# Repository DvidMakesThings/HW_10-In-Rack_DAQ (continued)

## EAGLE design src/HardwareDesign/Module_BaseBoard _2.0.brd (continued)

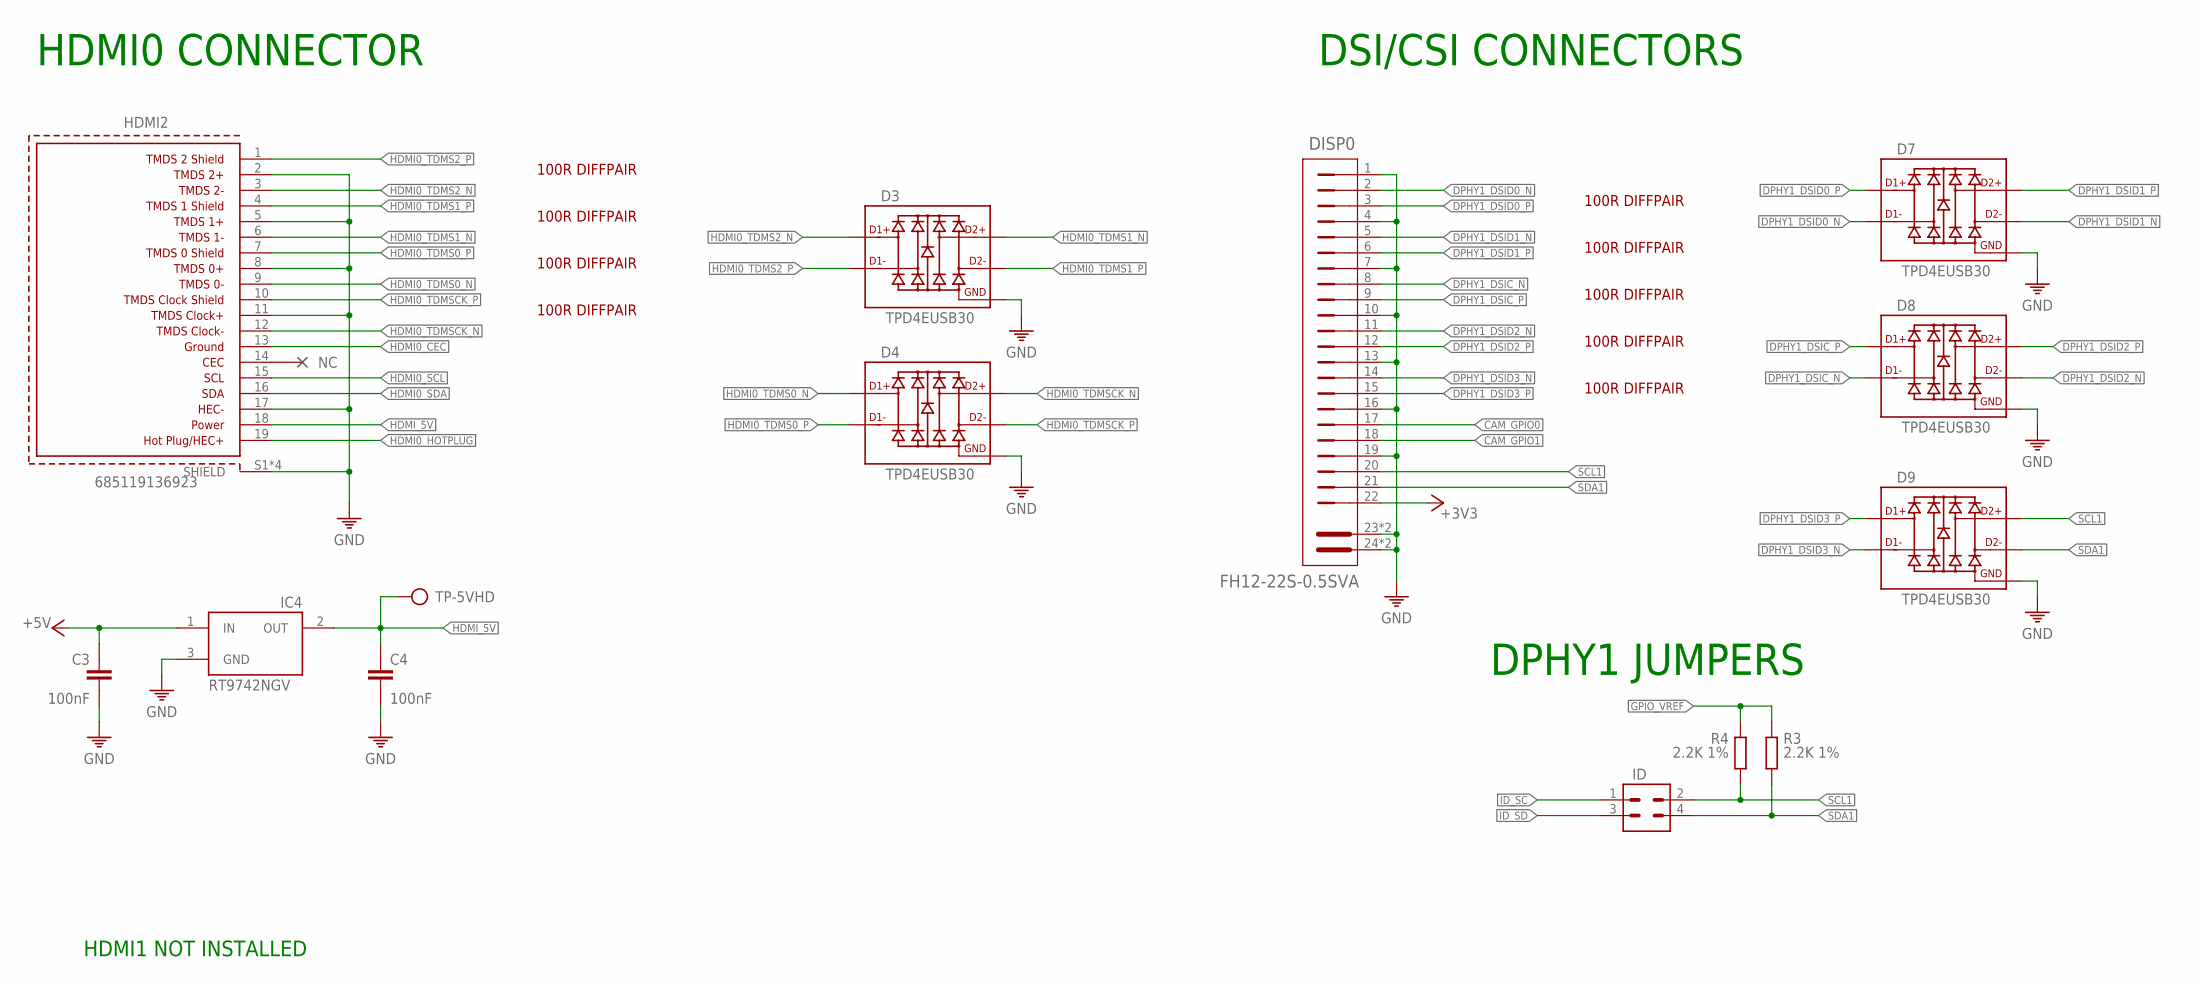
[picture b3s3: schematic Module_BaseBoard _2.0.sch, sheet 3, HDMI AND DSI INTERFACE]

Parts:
C3, C4: 100nF; C0402
D3, D4, D7, D8, D9: TPD4EUSB30; USON
DISP0: FH12-22S-0.5SVA; FH12-22S-0.5SH
HDMI2: 685119136923
IC4: RT9742NGV; SOT23
ID: CON-2X2; 2X2
R3, R4: 2.2K 1%; 0402
TP-5VHD: TP

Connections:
+3V3: DISP0.22; also elsewhere on the board
+5V: C3.1, IC4.1 (IN); also elsewhere on the board
CAM_GPIO0: DISP0.17; also elsewhere on the board
CAM_GPIO1: DISP0.18; also elsewhere on the board
DPHY1_DSIC_N: D8.5 (D2-), D8.6 (D2-), DISP0.8; also elsewhere on the board
DPHY1_DSIC_P: D8.4 (D2+), D8.7 (D2+), DISP0.9; also elsewhere on the board
DPHY1_DSID0_N: D7.5 (D2-), D7.6 (D2-), DISP0.2; also elsewhere on the board
DPHY1_DSID0_P: D7.4 (D2+), D7.7 (D2+), DISP0.3; also elsewhere on the board
DPHY1_DSID1_N: D7.2 (D1-), D7.9 (D1-), DISP0.5; also elsewhere on the board
DPHY1_DSID1_P: D7.1 (D1+), D7.10 (D1+), DISP0.6; also elsewhere on the board
DPHY1_DSID2_N: D8.2 (D1-), D8.9 (D1-), DISP0.11; also elsewhere on the board
DPHY1_DSID2_P: D8.1 (D1+), D8.10 (D1+), DISP0.12; also elsewhere on the board
DPHY1_DSID3_N: D9.5 (D2-), D9.6 (D2-), DISP0.14; also elsewhere on the board
DPHY1_DSID3_P: D9.4 (D2+), D9.7 (D2+), DISP0.15; also elsewhere on the board
GND: C3.2, C4.2, D3.3 (GND), D3.8 (GND), D4.3 (GND), D4.8 (GND), D7.3 (GND), D7.8 (GND), D8.3 (GND), D8.8 (GND), D9.3 (GND), D9.8 (GND), DISP0.1, DISP0.4, DISP0.7, DISP0.10, DISP0.13, DISP0.16, DISP0.19, DISP0.23 (MH1), DISP0.24 (MH2), DISP0.25 (MH1), DISP0.26 (MH2), HDMI2.2 (TMDS2+), HDMI2.5 (TMDSDATA1+), HDMI2.8 (TMDS0+), HDMI2.11 (TMDSCLOCK+), HDMI2.17 (UTILITY/HEAC+), HDMI2.S1 (SHIELD), HDMI2.S2 (SHIELD), HDMI2.S3 (SHIELD), HDMI2.S4 (SHIELD), IC4.3 (GND); also elsewhere on the board
GPIO_VREF: R3.1, R4.1; also elsewhere on the board
HDMI0_CEC: HDMI2.13 (GROUND); also elsewhere on the board
HDMI0_HOTPLUG: HDMI2.19 (HOTPLUG/HEC+); also elsewhere on the board
HDMI0_SCL: HDMI2.15 (SCL); also elsewhere on the board
HDMI0_SDA: HDMI2.16 (SDA); also elsewhere on the board
HDMI0_TDMS0_N: D4.4 (D2+), D4.7 (D2+), HDMI2.9 (TMDS0-); also elsewhere on the board
HDMI0_TDMS0_P: D4.5 (D2-), D4.6 (D2-), HDMI2.7 (TMDS0SHIELD); also elsewhere on the board
HDMI0_TDMS1_N: D3.1 (D1+), D3.10 (D1+), HDMI2.6 (TMDS1-); also elsewhere on the board
HDMI0_TDMS1_P: D3.2 (D1-), D3.9 (D1-), HDMI2.4 (TMDS1SHIELD); also elsewhere on the board
HDMI0_TDMS2_N: D3.4 (D2+), D3.7 (D2+), HDMI2.3 (TMDS2-); also elsewhere on the board
HDMI0_TDMS2_P: D3.5 (D2-), D3.6 (D2-), HDMI2.1 (TMDS2SHIELD); also elsewhere on the board
HDMI0_TDMSCK_N: D4.1 (D1+), D4.10 (D1+), HDMI2.12 (TMDSCLOCK-); also elsewhere on the board
HDMI0_TDMSCK_P: D4.2 (D1-), D4.9 (D1-), HDMI2.10 (TMDSCLOCKSHIELD); also elsewhere on the board
HDMI_5V: C4.1, HDMI2.18 (POWER), IC4.2 (OUT), TP-5VHD.TP
ID_SC: ID.1; also elsewhere on the board
ID_SD: ID.3; also elsewhere on the board
SCL1: D9.1 (D1+), D9.10 (D1+), DISP0.20, ID.2, R4.2
SDA1: D9.2 (D1-), D9.9 (D1-), DISP0.21, ID.4, R3.2

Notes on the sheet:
HDMI0 CONNECTOR
100R DIFFPAIR
DSI/CSI CONNECTORS
DPHY1 JUMPERS
HDMI1 NOT INSTALLED

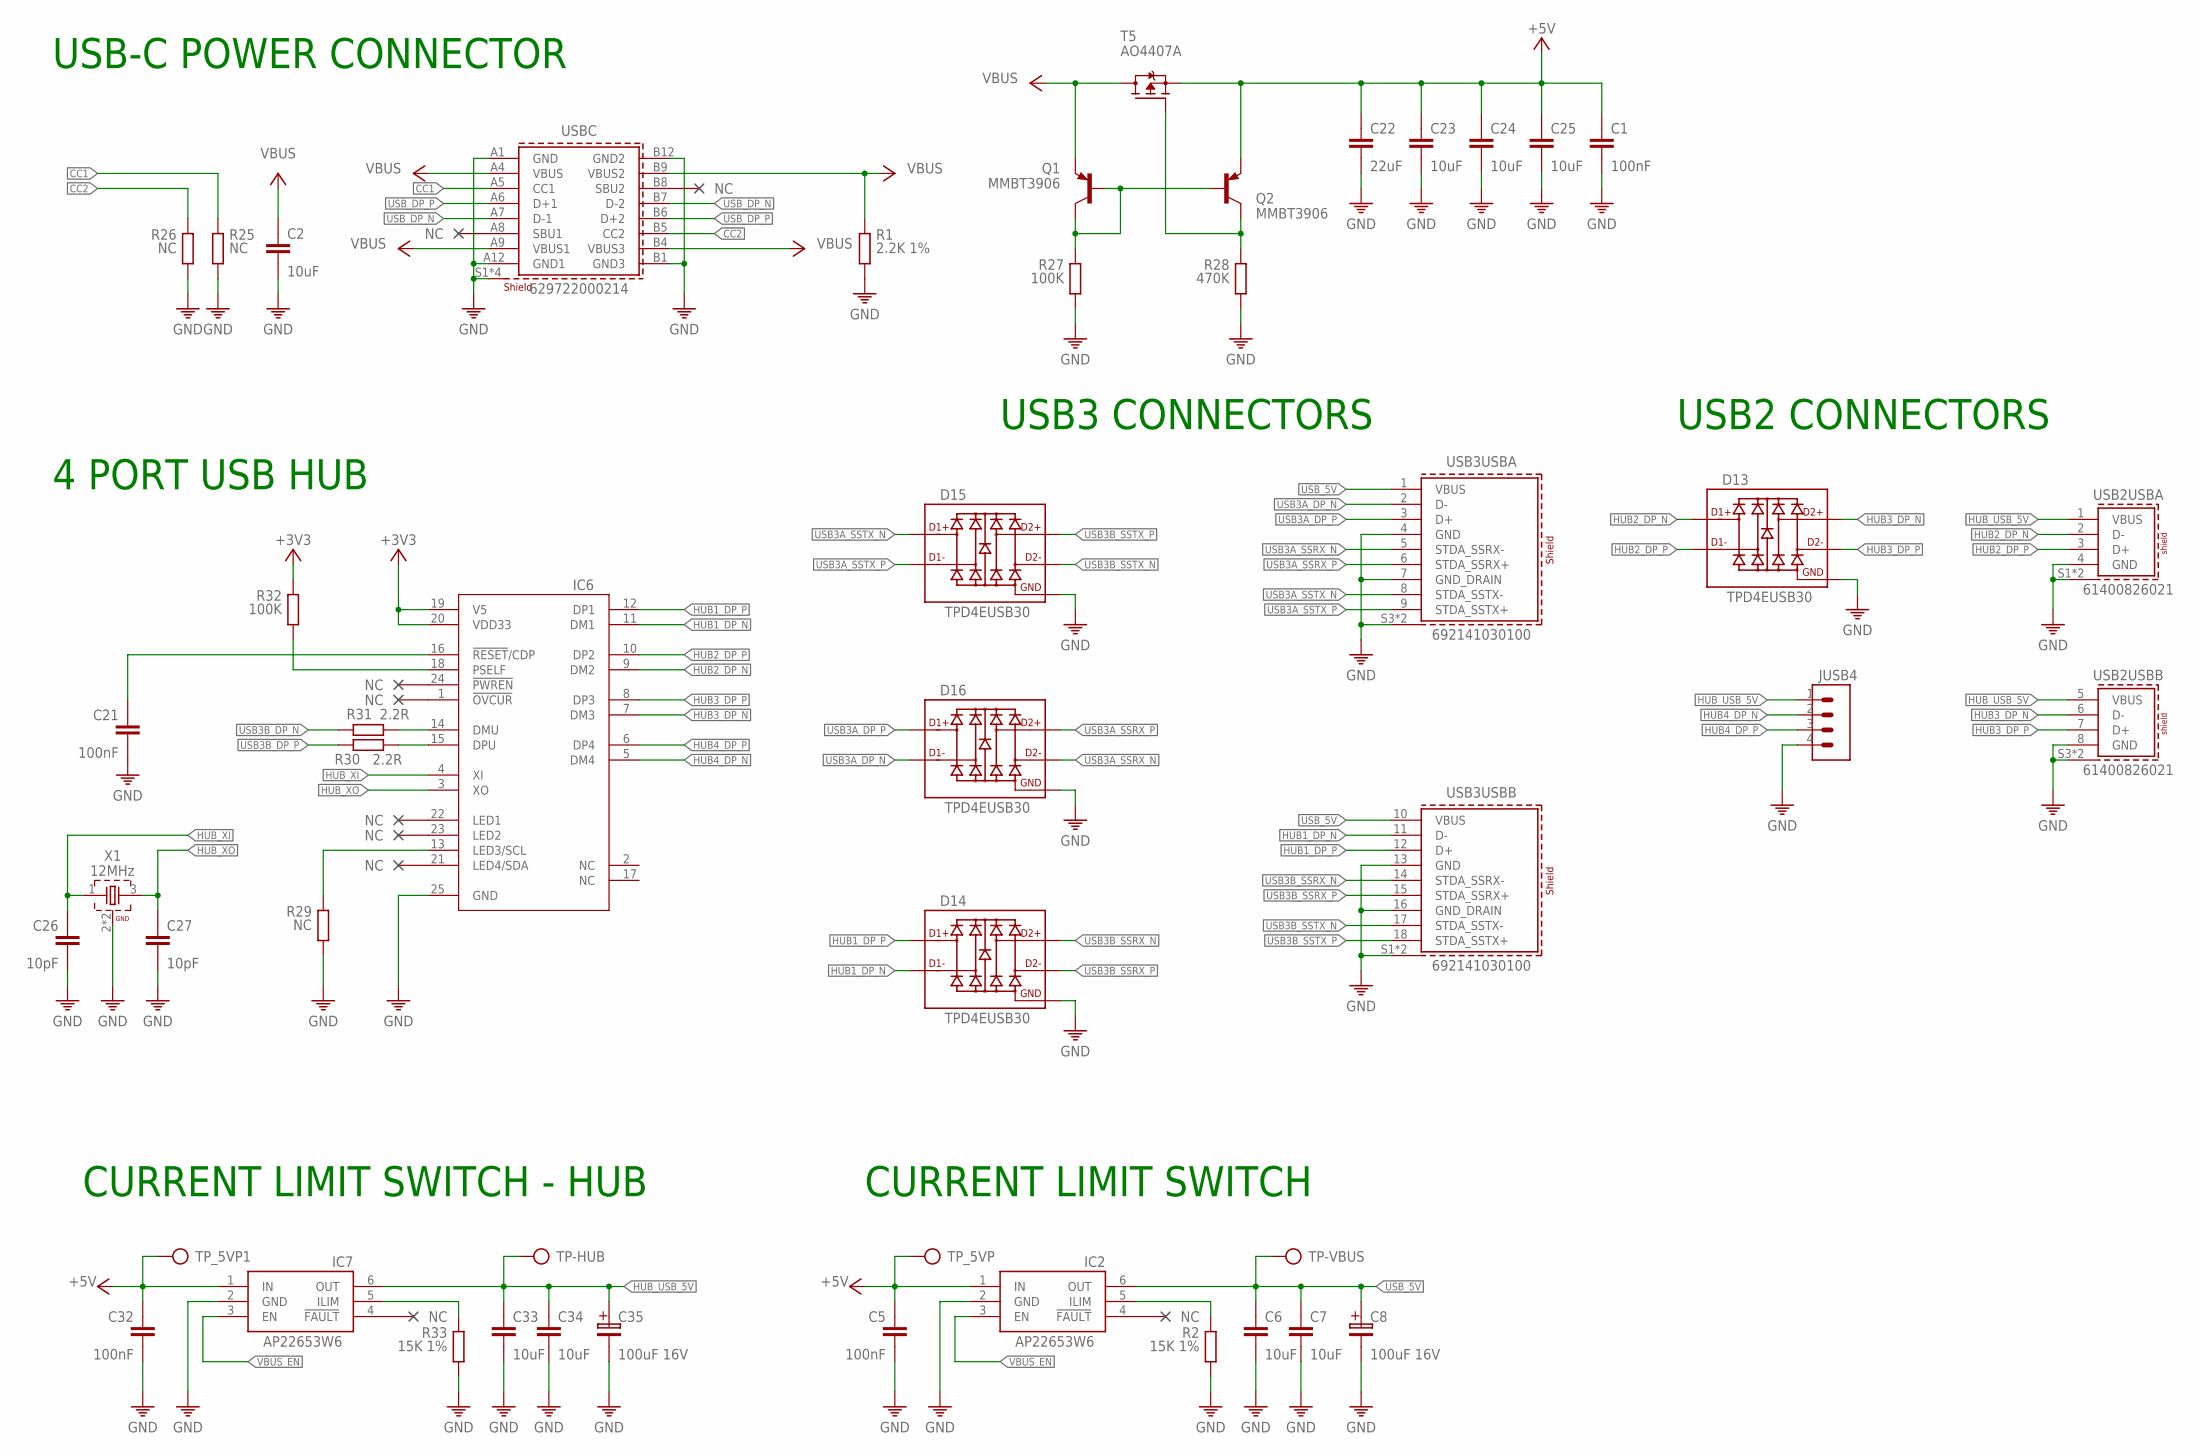
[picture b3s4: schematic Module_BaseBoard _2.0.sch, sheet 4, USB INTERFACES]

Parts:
C1: 100nF; C0805
C2, C6, C7, C23, C24, C25, C33, C34: 10uF; C0805
C5, C21, C32: 100nF; C0402
C8, C35: 100uF 16V; 100UF-16V
C22: 22uF; C0805
C26, C27: 10pF; C0402
D13, D14, D15, D16: TPD4EUSB30; USON
IC2, IC7: AP22653W6; SOT23-6
IC6: CH334; QFN24
JUSB4: CON-1X4; 1X4
Q1, Q2: MMBT3906; SOT23
R1: 2.2K 1%; 0402
R2, R33: 15K 1%; 0402
R25, R26, R29: NC; 0402
R27, R32: 100K; 0402
R28: 470K; 0402
R30, R31: 2.2R; 0402
T5: AO4407A; SO8
TP-HUB: TP
TP-VBUS: TP
TP_5VP, TP_5VP1: TP
USB2: 61400826021
USB3: 692141030100
USBC: 629722000214
X1: 12MHz; WE-XTAL_CFPX-180

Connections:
+3V3: IC6.19 (V5), IC6.20 (VDD33), R32.1; also elsewhere on the board
+5V: C1.1, C5.1, C22.1, C23.1, C24.1, C25.1, C32.1, IC2.1 (IN), IC7.1 (IN), Q2.2 (E), T5.1 (S), T5.2 (S), T5.3 (S), TP_5VP.TP, TP_5VP1.TP; also elsewhere on the board
CC1: R25.1, USBC.A5 (CC1); also elsewhere on the board
CC2: R26.1, USBC.B5 (CC2); also elsewhere on the board
GND: C1.2, C2.2, C5.2, C6.2, C7.2, C8.2, C21.2, C22.2, C23.2, C24.2, C25.2, C26.2, C27.2, C32.2, C33.2, C34.2, C35.2, D13.3 (GND), D13.8 (GND), D14.3 (GND), D14.8 (GND), D15.3 (GND), D15.8 (GND), D16.3 (GND), D16.8 (GND), IC2.2 (GND), IC6.25 (GND), IC7.2 (GND), JUSB4.4, R1.2, R2.2, R25.2, R26.2, R27.2, R28.2, R29.2, R33.2, USB2.4 (GND), USB2.8 (GND), USB2.S1 (SHIELD), USB2.S2 (SHIELD), USB2.S3 (SHIELD), USB2.S4 (SHIELD), USB3.4 (GND), USB3.7 (GND_DRAIN), USB3.13 (GND), USB3.16 (GND_DRAIN), USB3.S1 (SHIELD), USB3.S2 (SHIELD), USB3.S3 (SHIELD), USB3.S4 (SHIELD), USBC.A1 (GND), USBC.A12 (GND1), USBC.B1 (GND3), USBC.B12 (GND2), USBC.S1 (SHIELD), USBC.S2 (SHIELD), USBC.S3 (SHIELD), USBC.S4 (SHIELD), X1.2 (GND), X1.4 (GND); also elsewhere on the board
HUB1_DP_N: D14.5 (D2-), D14.6 (D2-), IC6.11 (DM1), USB3.11 (D-)
HUB1_DP_P: D14.4 (D2+), D14.7 (D2+), IC6.12 (DP1), USB3.12 (D+)
HUB2_DP_N: D13.4 (D2+), D13.7 (D2+), IC6.9 (DM2), USB2.2 (D-)
HUB2_DP_P: D13.5 (D2-), D13.6 (D2-), IC6.10 (DP2), USB2.3 (D+)
HUB3_DP_N: D13.1 (D1+), D13.10 (D1+), IC6.7 (DM3), USB2.6 (D-)
HUB3_DP_P: D13.2 (D1-), D13.9 (D1-), IC6.8 (DP3), USB2.7 (D+)
HUB4_DP_N: IC6.5 (DM4), JUSB4.2
HUB4_DP_P: IC6.6 (DP4), JUSB4.3
HUB_USB_5V: C33.1, C34.1, C35.1, IC7.6 (OUT), JUSB4.1, TP-HUB.TP, USB2.1 (VBUS), USB2.5 (VBUS)
HUB_XI: C26.1, IC6.4 (XI), X1.1
HUB_XO: C27.1, IC6.3 (XO), X1.3 (2)
unnamed: IC2.5 (ILIM), R2.1
unnamed: C21.1, IC6.16 (!RESET!/CDP)
unnamed: Q1.1 (B), Q1.3 (C), Q2.1 (B), R27.1
unnamed: Q2.3 (C), R28.1, T5.4 (G)
unnamed: IC6.18 (PSELF), R32.2
unnamed: IC6.13 (LED3/SCL), R29.1
unnamed: IC7.5 (ILIM), R33.1
USB3A_DP_N: D16.5 (D2-), D16.6 (D2-), USB3.2 (D-); also elsewhere on the board
USB3A_DP_P: D16.4 (D2+), D16.7 (D2+), USB3.3 (D+); also elsewhere on the board
USB3A_SSRX_N: D16.2 (D1-), D16.9 (D1-), USB3.5 (STDA_SSRX-); also elsewhere on the board
USB3A_SSRX_P: D16.1 (D1+), D16.10 (D1+), USB3.6 (STDA_SSRX+); also elsewhere on the board
USB3A_SSTX_N: D15.4 (D2+), D15.7 (D2+), USB3.8 (STDA_SSTX-); also elsewhere on the board
USB3A_SSTX_P: D15.5 (D2-), D15.6 (D2-), USB3.9 (STDA_SSTX+); also elsewhere on the board
USB3B2_DP_N: IC6.14 (DMU), R31.2
USB3B2_DP_P: IC6.15 (DPU), R30.2
USB3B_DP_N: R31.1; also elsewhere on the board
USB3B_DP_P: R30.1; also elsewhere on the board
USB3B_SSRX_N: D14.1 (D1+), D14.10 (D1+), USB3.14 (STDA_SSRX-); also elsewhere on the board
USB3B_SSRX_P: D14.2 (D1-), D14.9 (D1-), USB3.15 (STDA_SSRX+); also elsewhere on the board
USB3B_SSTX_N: D15.2 (D1-), D15.9 (D1-), USB3.17 (STDA_SSTX-); also elsewhere on the board
USB3B_SSTX_P: D15.1 (D1+), D15.10 (D1+), USB3.18 (STDA_SSTX+); also elsewhere on the board
USB_5V: C6.1, C7.1, C8.1, IC2.6 (OUT), TP-VBUS.TP, USB3.1 (VBUS), USB3.10 (VBUS)
USB_DP_N: USBC.A7 (D-1), USBC.B7 (D-2); also elsewhere on the board
USB_DP_P: USBC.A6 (D+1), USBC.B6 (D+2); also elsewhere on the board
VBUS: C2.1, Q1.2 (E), R1.1, T5.5 (D), T5.6 (D), T5.7 (D), T5.8 (D), USBC.A4 (VBUS), USBC.A9 (VBUS1), USBC.B4 (VBUS3), USBC.B9 (VBUS2)
VBUS_EN: IC2.3 (EN), IC7.3 (EN); also elsewhere on the board

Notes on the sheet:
USB-C POWER CONNECTOR
USB3 CONNECTORS
CURRENT LIMIT SWITCH
4 PORT USB HUB
USB2 CONNECTORS
CURRENT LIMIT SWITCH - HUB

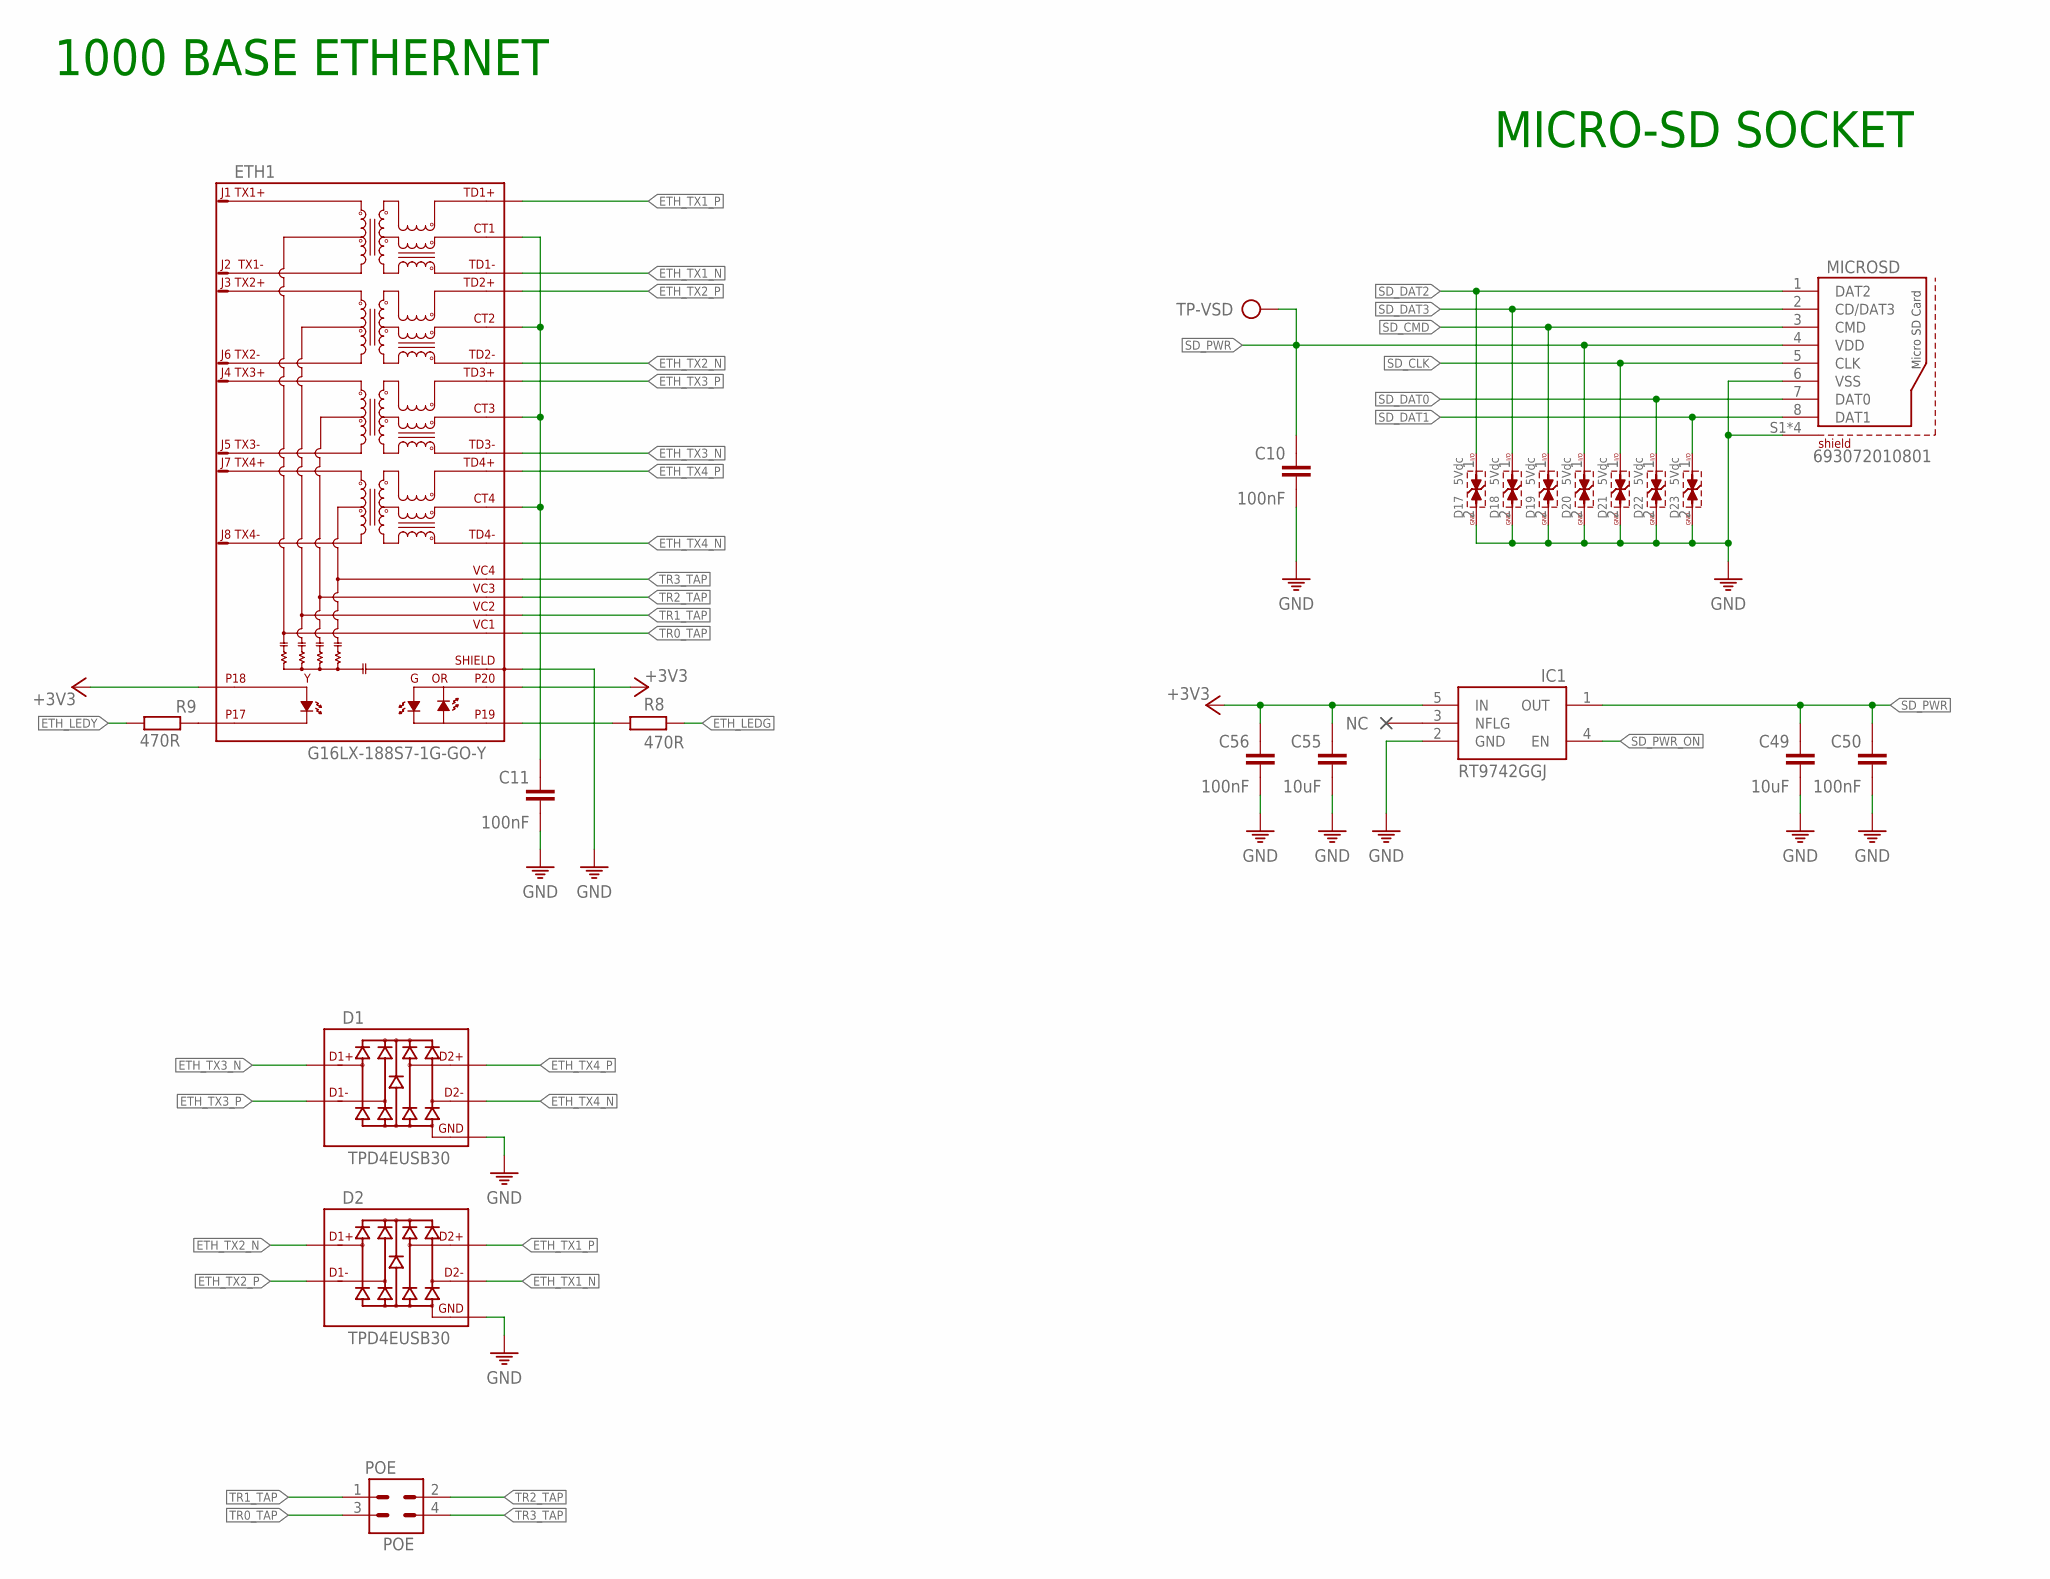
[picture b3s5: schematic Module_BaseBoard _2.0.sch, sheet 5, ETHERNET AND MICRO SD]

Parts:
C10, C50, C56: 100nF; C0402
C11: 100nF; C1206
C49, C55: 10uF; C0805
D1, D2: TPD4EUSB30; USON
D17, D18, D19, D20, D21, D22, D23: 5Vdc; WE-TVS_DFN1610-2L
ETH1: G16LX-188S7-1G-GO-Y; RJ45-CAT6-POE
IC1: RT9742GGJ; SOT23-5
MICROSD: 693072010801
POE: POE; 2X2
R8, R9: 470R; 0402
TP-VSD: TP

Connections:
+3V3: C55.1, C56.1, ETH1.18, ETH1.20, IC1.5 (IN); also elsewhere on the board
ETH_LEDG: R8.1; also elsewhere on the board
ETH_LEDY: R9.2; also elsewhere on the board
ETH_TX1_N: D2.2 (D1-), D2.9 (D1-), ETH1.TD1-; also elsewhere on the board
ETH_TX1_P: D2.1 (D1+), D2.10 (D1+), ETH1.TD1+; also elsewhere on the board
ETH_TX2_N: D2.4 (D2+), D2.7 (D2+), ETH1.TD2-; also elsewhere on the board
ETH_TX2_P: D2.5 (D2-), D2.6 (D2-), ETH1.TD2+; also elsewhere on the board
ETH_TX3_N: D1.4 (D2+), D1.7 (D2+), ETH1.TD3-; also elsewhere on the board
ETH_TX3_P: D1.5 (D2-), D1.6 (D2-), ETH1.TD3+; also elsewhere on the board
ETH_TX4_N: D1.2 (D1-), D1.9 (D1-), ETH1.TD4-; also elsewhere on the board
ETH_TX4_P: D1.1 (D1+), D1.10 (D1+), ETH1.TD4+; also elsewhere on the board
GND: C10.2, C11.2, C49.2, C50.2, C55.2, C56.2, D1.3 (GND), D1.8 (GND), D2.3 (GND), D2.8 (GND), D17.2 (GND), D18.2 (GND), D19.2 (GND), D20.2 (GND), D21.2 (GND), D22.2 (GND), D23.2 (GND), ETH1.MH3 (SHIELD), ETH1.MH4 (SHIELD), IC1.2 (GND), MICROSD.6 (VSS), MICROSD.S1 (SHIELD), MICROSD.S2 (SHIELD), MICROSD.S3 (SHIELD), MICROSD.S4 (SHIELD); also elsewhere on the board
unnamed: C11.1, ETH1.CT1, ETH1.CT2, ETH1.CT3, ETH1.CT4
unnamed: ETH1.17, R9.1
unnamed: ETH1.19, R8.2
SD_CLK: D21.1 (I/O), MICROSD.5 (CLK); also elsewhere on the board
SD_CMD: D19.1 (I/O), MICROSD.3 (CMD); also elsewhere on the board
SD_DAT0: D22.1 (I/O), MICROSD.7 (DAT0); also elsewhere on the board
SD_DAT1: D23.1 (I/O), MICROSD.8 (DAT1); also elsewhere on the board
SD_DAT2: D17.1 (I/O), MICROSD.1 (DAT2); also elsewhere on the board
SD_DAT3: D18.1 (I/O), MICROSD.2 (CD/DAT3); also elsewhere on the board
SD_PWR: C10.1, C49.1, C50.1, D20.1 (I/O), IC1.1 (OUT), MICROSD.4 (VDD), TP-VSD.TP
SD_PWR_ON: IC1.4 (EN); also elsewhere on the board
TR0_TAP: ETH1.VC1, POE.3
TR1_TAP: ETH1.VC2, POE.1
TR2_TAP: ETH1.VC3, POE.2
TR3_TAP: ETH1.VC4, POE.4

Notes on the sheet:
1000 BASE ETHERNET
MICRO-SD SOCKET

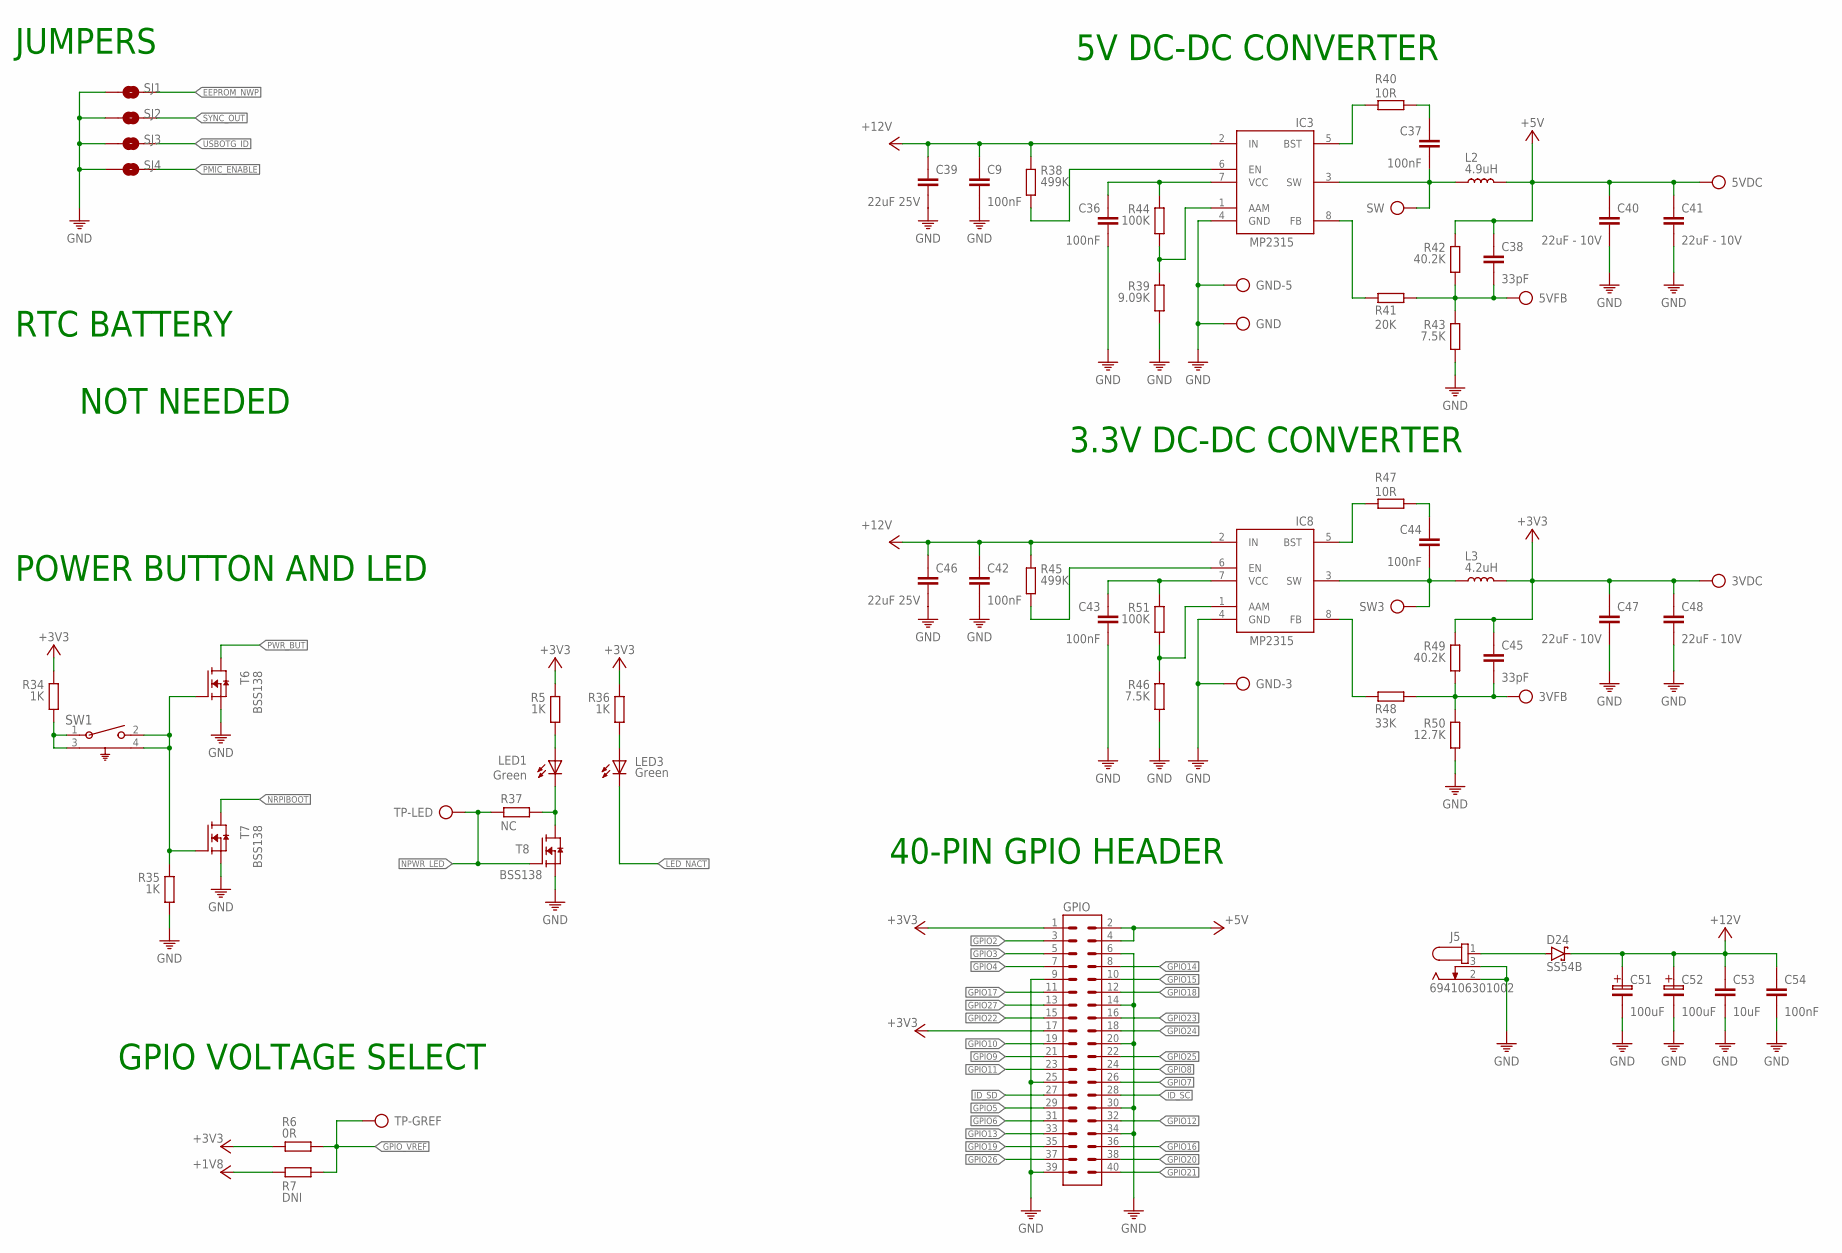
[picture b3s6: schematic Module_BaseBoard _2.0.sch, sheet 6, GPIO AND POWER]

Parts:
3VDC, 3VFB, 5VDC, 5VFB: TP
C9, C36, C37, C42, C43, C44: 100nF; 0402
C38, C45: 33pF; 0402
C39, C46: 22uF 25V; C1206
C40, C41, C47, C48: 22uF - 10V; C1206
C51, C52: 100uF; 100UF-16V
C53: 10uF; C1206
C54: 100nF; C1206
D24: SS54B; SMB
GND: TP
GND-3, GND-5: TP
GPIO: CON-2X20; 2X20
IC3: MP2315GJ-Z; SOT65P280X110-8N
IC8: MP2315S; SOT65P280X110-8N
J5: 694106301002
L2: 4.9uH; SRR5228A
L3: 4.2uH; SRR5228A
LED1, LED3: Green; CHIPLED_0805
R5, R34, R35, R36: 1K; 0402
R6: 0R; 0402
R7: DNI; 0402
R37: NC; 0402
R38, R45: 499K; 0402
R39: 9.09K; 0402
R40, R47: 10R; 0402
R41: 20K; 0402
R42, R49: 40.2K; 0402
R43, R46: 7.5K; 0402
R44, R51: 100K; 0402
R48: 33K; 0402
R50: 12.7K; 0402
SJ1, SJ2, SJ3, SJ4: SOLDERJUMPERNO; SJ_2S-NO
SW, SW3: TP
SW1: 1825027-8; SW2_1825027-C_TEC
T6, T7, T8: BSS138; SOT23
TP-GREF: TP
TP-LED: TP

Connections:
5VFB: 5VFB.TP, C38.2, R41.2, R42.2, R43.1
+1V8: R7.1; also elsewhere on the board
+3V3: 3VDC.TP, C45.1, C47.1, C48.1, GPIO.1, GPIO.17, L3.2, R5.1, R6.1, R34.1, R36.1, R49.1; also elsewhere on the board
+5V: 5VDC.TP, C38.1, C40.1, C41.1, GPIO.2, GPIO.4, L2.2, R42.1; also elsewhere on the board
+12V: C9.1, C39.1, C42.1, C46.1, C51.1, C52.1, C53.1, C54.1, D24.C, IC3.2 (IN), IC8.2 (IN), R38.1, R45.1
EEPROM_NWP: SJ1.2; also elsewhere on the board
GND: C9.2, C36.2, C39.2, C40.2, C41.2, C42.2, C43.2, C46.2, C47.2, C48.2, C51.2, C52.2, C53.2, C54.2, GND.TP, GND-3.TP, GND-5.TP, GPIO.6, GPIO.9, GPIO.14, GPIO.20, GPIO.25, GPIO.30, GPIO.34, GPIO.39, IC3.4 (GND), IC8.4 (GND), J5.2, J5.3, R35.2, R39.2, R43.2, R46.2, R50.2, SJ1.1, SJ2.1, SJ3.1, SJ4.1, T6.2 (S), T7.2 (S), T8.2 (S); also elsewhere on the board
GPIO2: GPIO.3; also elsewhere on the board
GPIO3: GPIO.5; also elsewhere on the board
GPIO4: GPIO.7; also elsewhere on the board
GPIO5: GPIO.29; also elsewhere on the board
GPIO6: GPIO.31; also elsewhere on the board
GPIO7: GPIO.26; also elsewhere on the board
GPIO8: GPIO.24; also elsewhere on the board
GPIO9: GPIO.21; also elsewhere on the board
GPIO10: GPIO.19; also elsewhere on the board
GPIO11: GPIO.23; also elsewhere on the board
GPIO12: GPIO.32; also elsewhere on the board
GPIO13: GPIO.33; also elsewhere on the board
GPIO14: GPIO.8; also elsewhere on the board
GPIO15: GPIO.10; also elsewhere on the board
GPIO16: GPIO.36; also elsewhere on the board
GPIO17: GPIO.11; also elsewhere on the board
GPIO18: GPIO.12; also elsewhere on the board
GPIO19: GPIO.35; also elsewhere on the board
GPIO20: GPIO.38; also elsewhere on the board
GPIO21: GPIO.40; also elsewhere on the board
GPIO22: GPIO.15; also elsewhere on the board
GPIO23: GPIO.16; also elsewhere on the board
GPIO24: GPIO.18; also elsewhere on the board
GPIO25: GPIO.22; also elsewhere on the board
GPIO26: GPIO.37; also elsewhere on the board
GPIO27: GPIO.13; also elsewhere on the board
GPIO_VREF: R6.2, R7.2, TP-GREF.TP; also elsewhere on the board
ID_SC: GPIO.28; also elsewhere on the board
ID_SD: GPIO.27; also elsewhere on the board
LED_NACT: LED3.C; also elsewhere on the board
unnamed: LED1.A, R5.2
unnamed: LED3.A, R36.2
unnamed: R34.2, SW1.1, SW1.3
unnamed: LED1.C, R37.2, T8.3 (D)
unnamed: R35.1, SW1.2, SW1.4, T6.1 (G), T7.1 (G)
unnamed: IC3.5 (BST), R40.2
unnamed: IC3.8 (FB), R41.1
unnamed: C37.1, R40.1
unnamed: IC3.6 (EN), R38.2
unnamed: C36.1, IC3.7 (VCC), R44.1
unnamed: D24.A, J5.1
unnamed: IC8.5 (BST), R47.2
unnamed: IC8.8 (FB), R48.1
unnamed: C44.1, R47.1
unnamed: 3VFB.TP, C45.2, R48.2, R49.2, R50.1
unnamed: IC8.6 (EN), R45.2
unnamed: C43.1, IC8.7 (VCC), R51.1
unnamed: IC3.1 (AAM), R39.1, R44.2
unnamed: IC8.1 (AAM), R46.1, R51.2
NPWR_LED: R37.1, T8.1 (G), TP-LED.TP; also elsewhere on the board
NRPIBOOT: T7.3 (D); also elsewhere on the board
PMIC_ENABLE: SJ4.2; also elsewhere on the board
PWR_BUT: T6.3 (D); also elsewhere on the board
SW3: C44.2, IC8.3 (SW), L3.1, SW3.TP
SW5: C37.2, IC3.3 (SW), L2.1, SW.TP
SYNC_OUT: SJ2.2; also elsewhere on the board
USBOTG_ID: SJ3.2; also elsewhere on the board

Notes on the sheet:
JUMPERS
RTC BATTERY
POWER BUTTON AND LED
GPIO VOLTAGE SELECT
40-PIN GPIO HEADER
NOT NEEDED
5V DC-DC CONVERTER
3.3V DC-DC CONVERTER

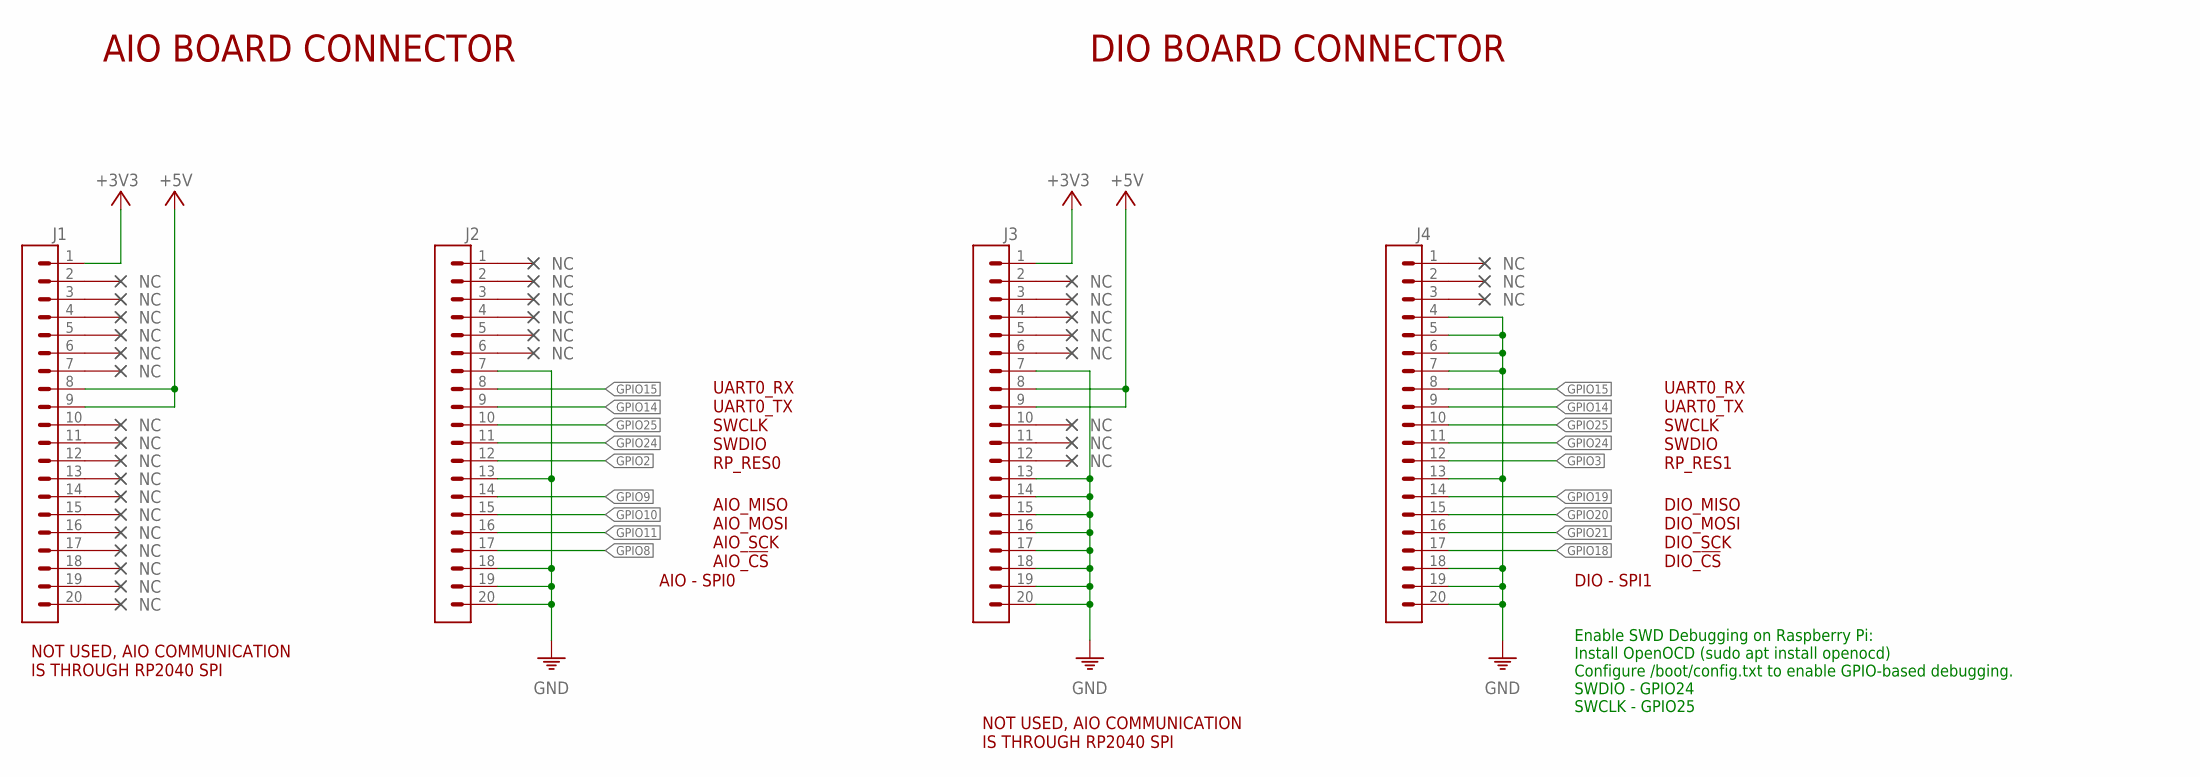
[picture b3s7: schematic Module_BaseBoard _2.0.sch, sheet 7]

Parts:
J1, J2, J3, J4: CON-1X20; 1X20

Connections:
+3V3: J1.1, J3.1; also elsewhere on the board
+5V: J1.8, J1.9, J3.8, J3.9; also elsewhere on the board
GND: J2.7, J2.13, J2.18, J2.19, J2.20, J3.7, J3.13, J3.14, J3.15, J3.16, J3.17, J3.18, J3.19, J3.20, J4.4, J4.5, J4.6, J4.7, J4.13, J4.18, J4.19, J4.20; also elsewhere on the board
GPIO2: J2.12; also elsewhere on the board
GPIO3: J4.12; also elsewhere on the board
GPIO8: J2.17; also elsewhere on the board
GPIO9: J2.14; also elsewhere on the board
GPIO10: J2.15; also elsewhere on the board
GPIO11: J2.16; also elsewhere on the board
GPIO14: J2.9, J4.9; also elsewhere on the board
GPIO15: J2.8, J4.8; also elsewhere on the board
GPIO18: J4.17; also elsewhere on the board
GPIO19: J4.14; also elsewhere on the board
GPIO20: J4.15; also elsewhere on the board
GPIO21: J4.16; also elsewhere on the board
GPIO24: J2.11, J4.11; also elsewhere on the board
GPIO25: J2.10, J4.10; also elsewhere on the board

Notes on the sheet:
AIO BOARD CONNECTOR
Enable SWD Debugging on Raspberry Pi: Install OpenOCD (sudo apt install openocd) Configure /boot/config.txt to enable GPIO-based debugging. SWDIO - GPIO24 SWCLK - GPIO25
DIO BOARD CONNECTOR
NOT USED, AIO COMMUNICATION IS THROUGH RP2040 SPI
AIO - SPI0
DIO - SPI1
UART0_RX UART0_TX SWCLK SWDIO RP_RES0
UART0_RX UART0_TX SWCLK SWDIO RP_RES1
AIO_MISO AIO_MOSI AIO_SCK AIO_!CS
DIO_MISO DIO_MOSI DIO_SCK DIO_!CS
